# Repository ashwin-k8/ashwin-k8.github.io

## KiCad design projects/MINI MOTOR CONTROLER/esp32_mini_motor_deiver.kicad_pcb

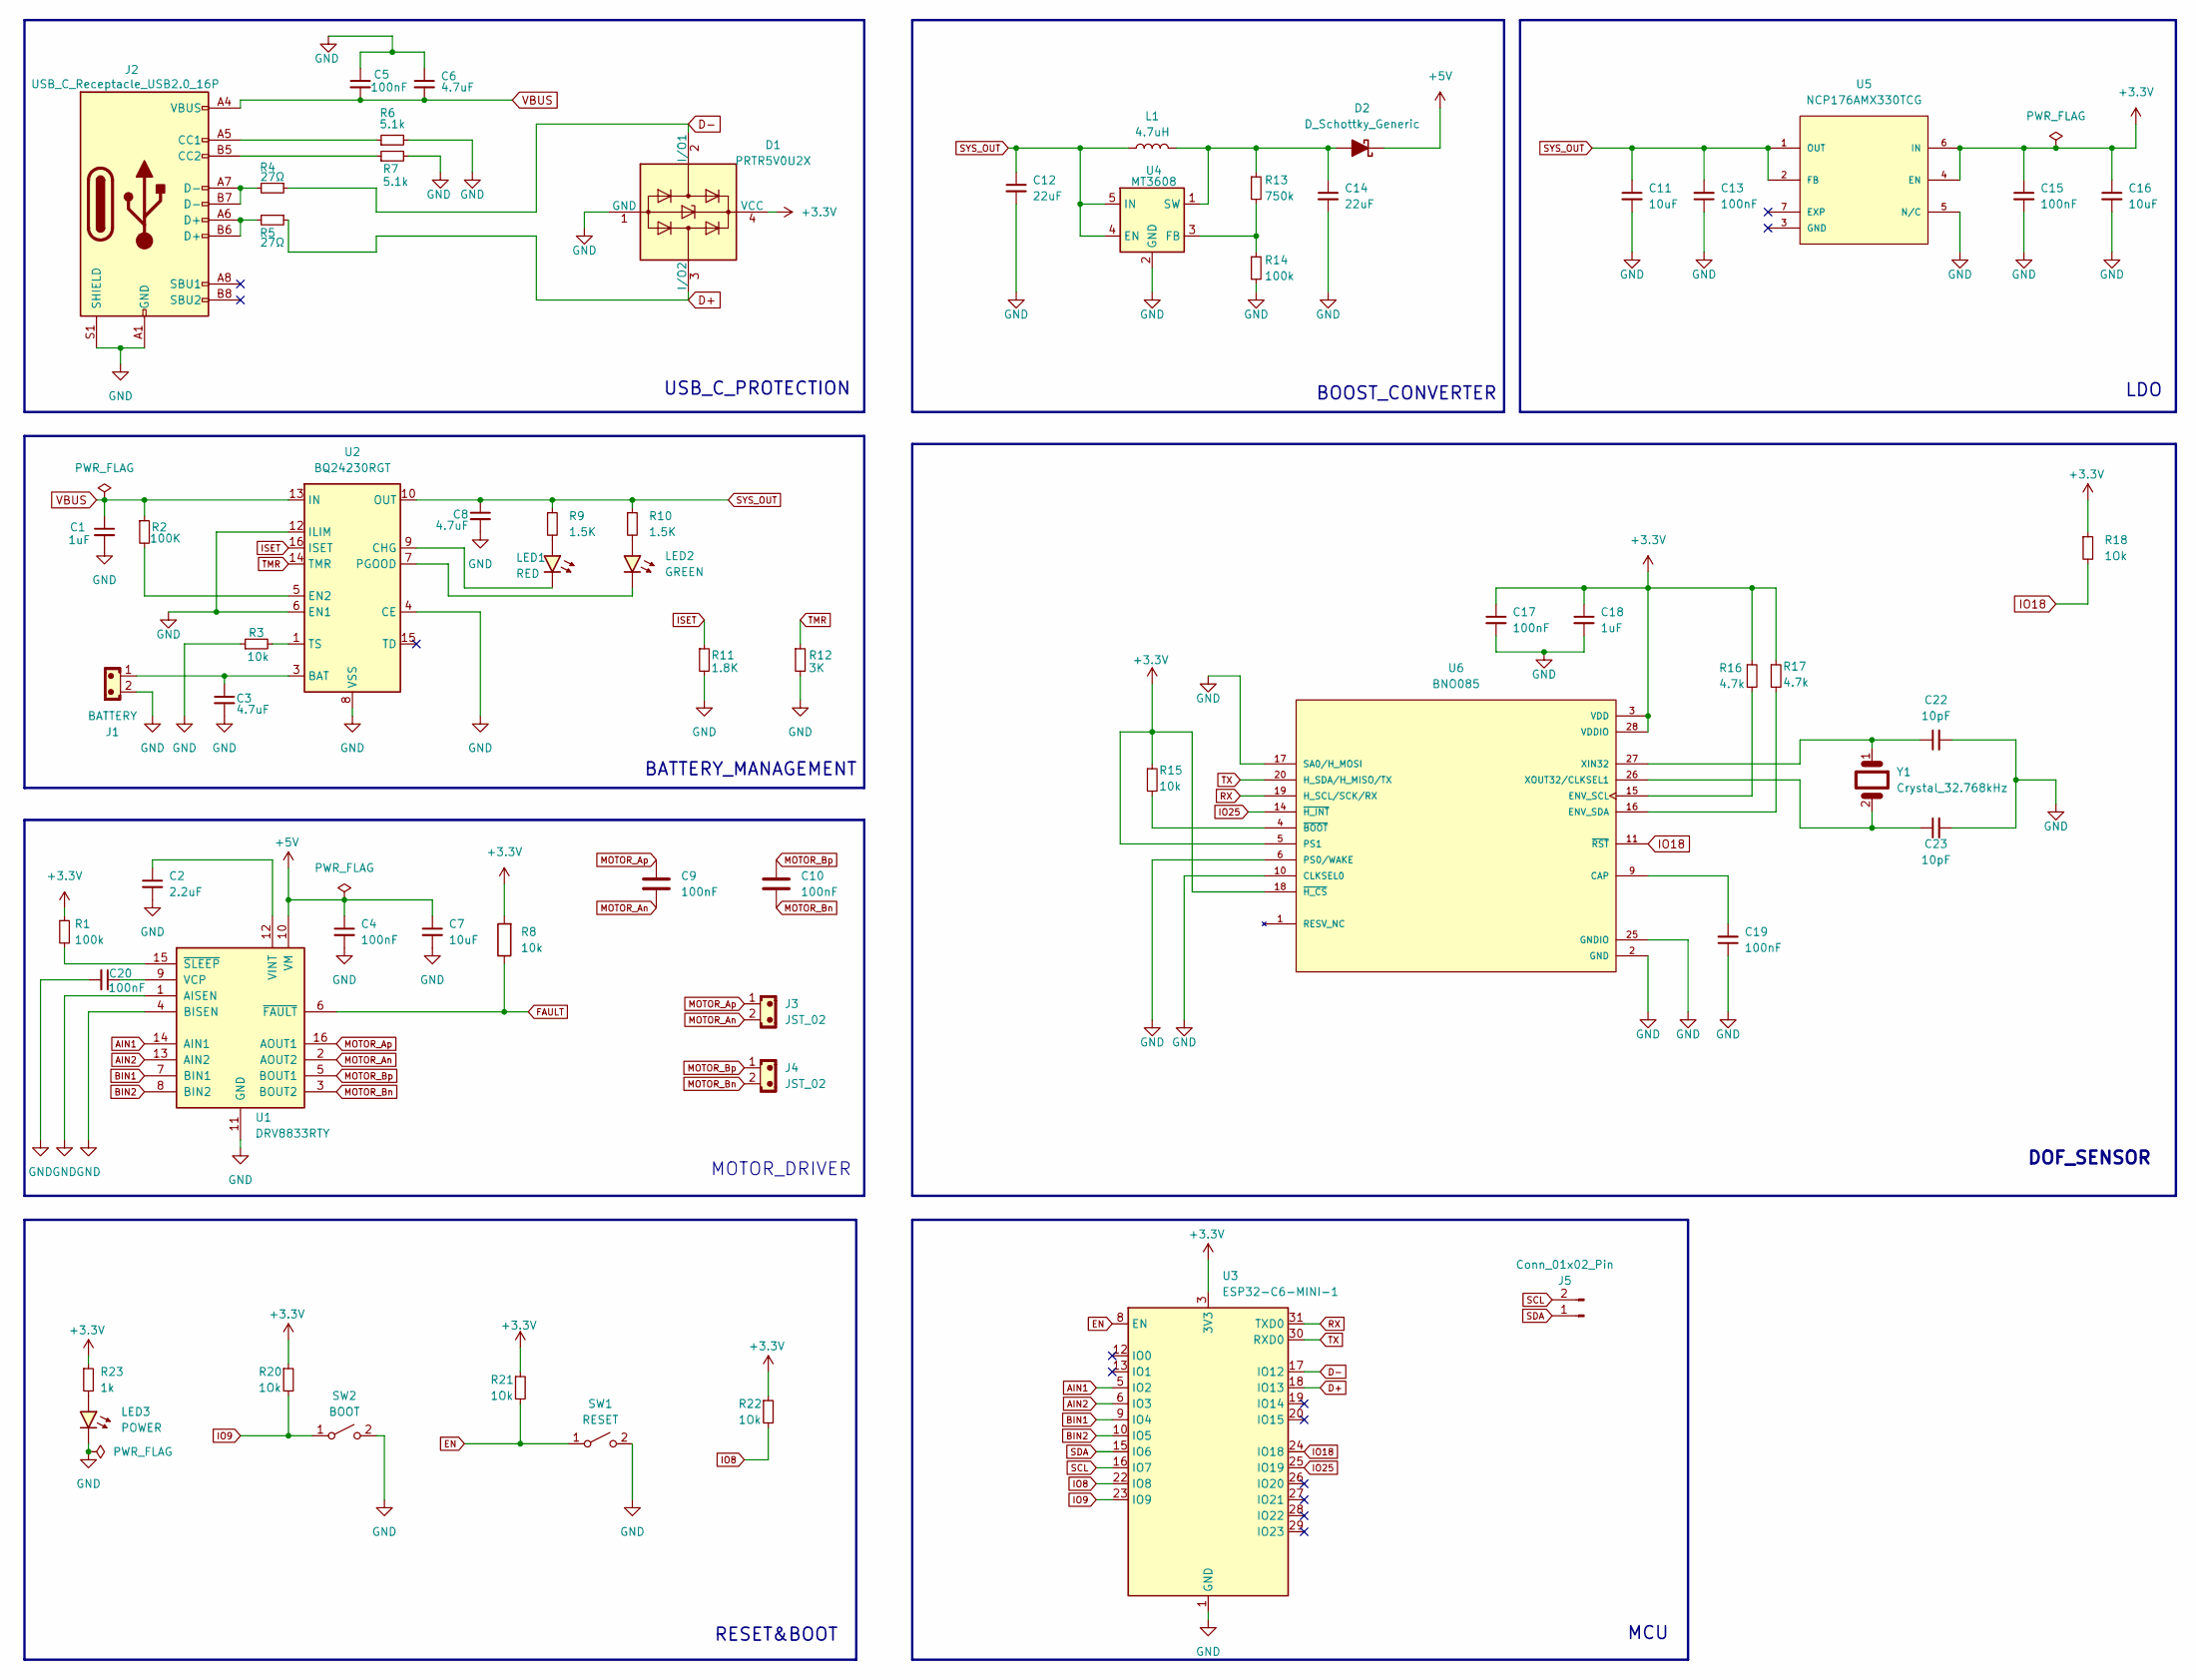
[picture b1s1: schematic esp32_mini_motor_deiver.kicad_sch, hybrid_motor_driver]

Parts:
C1: 1uF; C_0603_1608Metric
C2: 2.2uF; C_0603_1608Metric
C3, C6, C8: 4.7uF; C_0603_1608Metric
C4, C5: 100nF; C_0603_1608Metric
C7: 10uF; C_0603_1608Metric
C9, C10: 100nF; C_0402_1005Metric
C11, C16: 10uF; C_0805_2012Metric
C12, C14: 22uF; C_0805_2012Metric
C13, C15, C17, C19, C20: 100nF; C_0805_2012Metric
C18: 1uF; C_0805_2012Metric
C22, C23: 10pF; C_0805_2012Metric
D1: PRTR5V0U2X; SOT-143
D2: D_Schottky_Generic; D_0603_1608Metric
J1: BATTERY; JST_SH_SM02B-SRSS-TB_1x02-1MP_P1.00mm_Horizontal
J2: USB_C_Receptacle_USB2.0_16P; USB_C_Receptacle_XKB_U262-16XN-4BVC11
J3, J4: JST_02; JST_EH_B2B-EH-A_1x02_P2.50mm_Vertical
J5: Conn_01x02_Pin; PinHeader_1x02_P1.00mm_Vertical
L1: 4.7uH; L_0805_2012Metric
LED1: RED; LED_0603_1608Metric
LED2: GREEN; LED_0603_1608Metric
LED3: POWER; LED_0805_2012Metric
R1, R14: 100k; R_0805_2012Metric
R2: 100K; R_0805_2012Metric
R3, R8, R15: 10k; R_0805_2012Metric
R4, R5: 27Ω; R_0805_2012Metric
R6, R7: 5.1k; R_0805_2012Metric
R9, R10: 1.5K; R_0805_2012Metric
R11: 1.8K; R_0805_2012Metric
R12: 3K; R_0805_2012Metric
R13: 750k; R_0805_2012Metric
R16, R17: 4.7k; R_0805_2012Metric
R18, R20, R21, R22: 1Ok; R_0805_2012Metric
R23: 1k; R_0805_2012Metric
SW1: RESET; SW_SPST_B3U-1000P
SW2: BOOT; SW_SPST_B3U-1000P
U1: DRV8833RTY; Texas_RTY_WQFN-16-1EP_4x4mm_P0.65mm_EP2.1x2.1mm_ThermalVias
U2: BQ24230RGT; VQFN-16-1EP_3x3mm_P0.5mm_EP1.68x1.68mm_ThermalVias
U3: ESP32-C6-MINI-1
U4: MT3608; SOT-23-6
U5: NCP176AMX330TCG; PARTREV 5
U6: BNO085; PARTREV v1.17
Y1: Crystal_32.768kHz; Crystal_SMD_EuroQuartz_EQ161-2Pin_3.2x1.5mm

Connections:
+3.3V: C15.1, C16.1, C17.1, C18.1, D1.4 (VCC), R1.1, R8.2, R15.1, R16.1, R17.1, R18.1, R20.1, R21.1, R22.1, R23.1, U3.3 (3V3), U5.4 (EN), U5.6 (IN), U6.3 (VDD), U6.5 (PS1), U6.18 (~H_CS), U6.28 (VDDIO)
+5V: C4.1, C7.1, D2.1 (K), U1.10 (VM)
AIN1: U1.14 (AIN1), U3.5 (IO2)
AIN2: U1.13 (AIN2), U3.6 (IO3)
BIN1: U1.7 (BIN1), U3.9 (IO4)
BIN2: U1.8 (BIN2), U3.10 (IO5)
D+: D1.3 (I/O2), R5.1, U3.18 (IO13)
D-: D1.2 (I/O1), R4.1, U3.17 (IO12)
EN: R21.2, SW1.1 (A), U3.8 (EN)
FAULT: R8.1, U1.6 (~FAULT)
GND: C1.2, C2.2, C3.2, C4.2, C5.1, C6.1, C7.2, C8.2, C11.2, C12.2, C13.1, C14.2, C15.2, C16.2, C17.2, C18.2, C19.1, C20.2, C22.2, C23.2, D1.1 (GND), J1.2, J2.A1 (GND_A1), J2.A12 (GND_A12), J2.B1 (GND_B1), J2.B12 (GND_B12), J2.S1 (SHIELD), J2.SH (SHIELD_S1), LED3.1 (K), R3.1, R6.2, R7.2, R11.2, R12.2, R14.2, SW1.2 (B), SW2.2 (B), U1.1 (AISEN), U1.4 (BISEN), U1.11 (GND), U1.17 (GND), U2.4 (CE), U2.6 (EN1), U2.8 (VSS), U2.12 (ILIM), U2.17 (VSS), U3.1 (GND), U3.2 (GND), U3.11 (GND), U3.14 (GND), U3.36 (GND), U3.37 (GND), U3.38 (GND), U3.39 (GND), U3.40 (GND), U3.41 (GND), U3.42 (GND), U3.43 (GND), U3.44 (GND), U3.45 (GND), U3.46 (GND), U3.47 (GND), U3.48 (GND), U3.49 (GND), U3.50 (GND), U3.51 (GND), U3.52 (GND), U3.53 (GND), U4.2 (GND), U5.5 (N/C), U6.2 (GND), U6.6 (PS0/WAKE), U6.10 (CLKSEL0), U6.17 (SA0/H_MOSI), U6.25 (GNDIO); also elsewhere on the board
IO8: R22.2, U3.22 (IO8)
IO9: R20.2, SW2.1 (A), U3.23 (IO9); also elsewhere on the board
IO18: R18.2, U3.24 (IO18), U6.11 (~RST)
IO25: U3.25 (IO19), U6.14 (~H_INT)
ISET: R11.1, U2.16 (ISET)
MOTOR_An: C9.2, J3.2, U1.2 (AOUT2)
MOTOR_Ap: C9.1, J3.1, U1.16 (AOUT1)
MOTOR_Bn: C10.2, J4.2, U1.3 (BOUT2)
MOTOR_Bp: C10.1, J4.1, U1.5 (BOUT1)
unnamed: C3.1, J1.1, U2.2 (BAT), U2.3 (BAT)
unnamed: C14.1, D2.2 (A), L1.2, R13.1, U4.1 (SW)
unnamed: J2.A5 (CC1_A5), R6.1
unnamed: J2.B5 (CC2_B5), R7.1
unnamed: J2.A6 (D+_A6), J2.B6 (D+_B6), R5.2
unnamed: J2.A7 (D-_A7), J2.B7 (D-_B7), R4.2
unnamed: LED1.2 (A), R9.2
unnamed: LED1.1 (K), U2.9 (CHG)
unnamed: LED2.2 (A), R10.2
unnamed: LED2.1 (K), U2.7 (PGOOD)
unnamed: LED3.2 (A), R23.2
unnamed: C20.1, U1.9 (VCP)
unnamed: C2.1, U1.12 (VINT)
unnamed: R1.2, U1.15 (~SLEEP)
unnamed: R2.2, U2.5 (EN2)
unnamed: R3.2, U2.1 (TS)
unnamed: R13.2, R14.1, U4.3 (FB)
unnamed: C19.2, U6.9 (CAP)
unnamed: R16.2, U6.15 (ENV_SCL)
unnamed: R17.2, U6.16 (ENV_SDA)
unnamed: C22.1, U6.27 (XIN32), Y1.1
unnamed: C23.1, U6.26 (XOUT32/CLKSEL1), Y1.2
unnamed: R15.2, U6.4 (~BOOT)
RX: U3.31 (TXD0), U6.19 (H_SCL/SCK/RX)
SCL: J5.2, U3.16 (IO7)
SDA: J5.1, U3.15 (IO6)
SYS_OUT: C8.1, C11.1, C12.1, C13.2, L1.1, R9.1, R10.1, U2.10 (OUT), U2.11 (OUT), U4.4 (EN), U4.5 (IN), U5.1 (OUT), U5.2 (FB)
TMR: R12.1, U2.14 (TMR)
TX: U3.30 (RXD0), U6.20 (H_SDA/H_MISO/TX)
VBUS: C1.1, C5.2, C6.2, J2.A4 (VBUS_A4), J2.A9 (VBUS_A9), J2.B4 (VBUS_B4), J2.B9 (VBUS_B9), R2.1, U2.13 (IN)

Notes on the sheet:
DOF_SENSOR
BATTERY_MANAGEMENT
MOTOR_DRIVER
MCU
BOOST_CONVERTER
LDO
RESET&BOOT
USB_C_PROTECTION

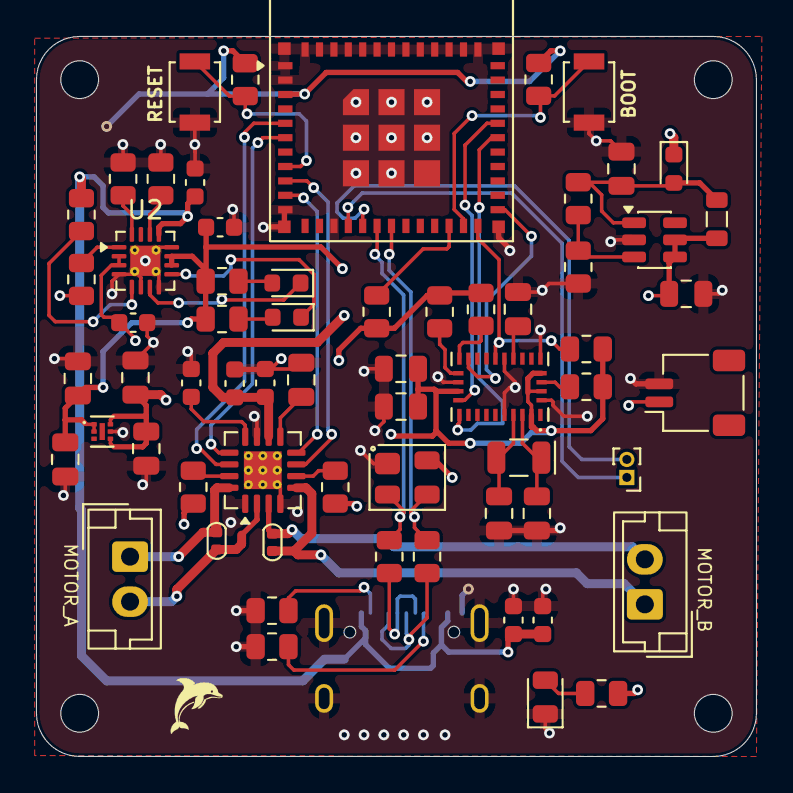
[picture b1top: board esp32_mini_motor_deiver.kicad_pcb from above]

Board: 4 copper layers, 40.0 x 40.0 mm, 64 parts (1 on the bottom side), 50 nets.

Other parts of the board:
BOOT: BOOT; SW_SPST_B3U-1000P

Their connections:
GND: BOOT.2 (B); also elsewhere on the board
IO9: BOOT.1 (A); also elsewhere on the board

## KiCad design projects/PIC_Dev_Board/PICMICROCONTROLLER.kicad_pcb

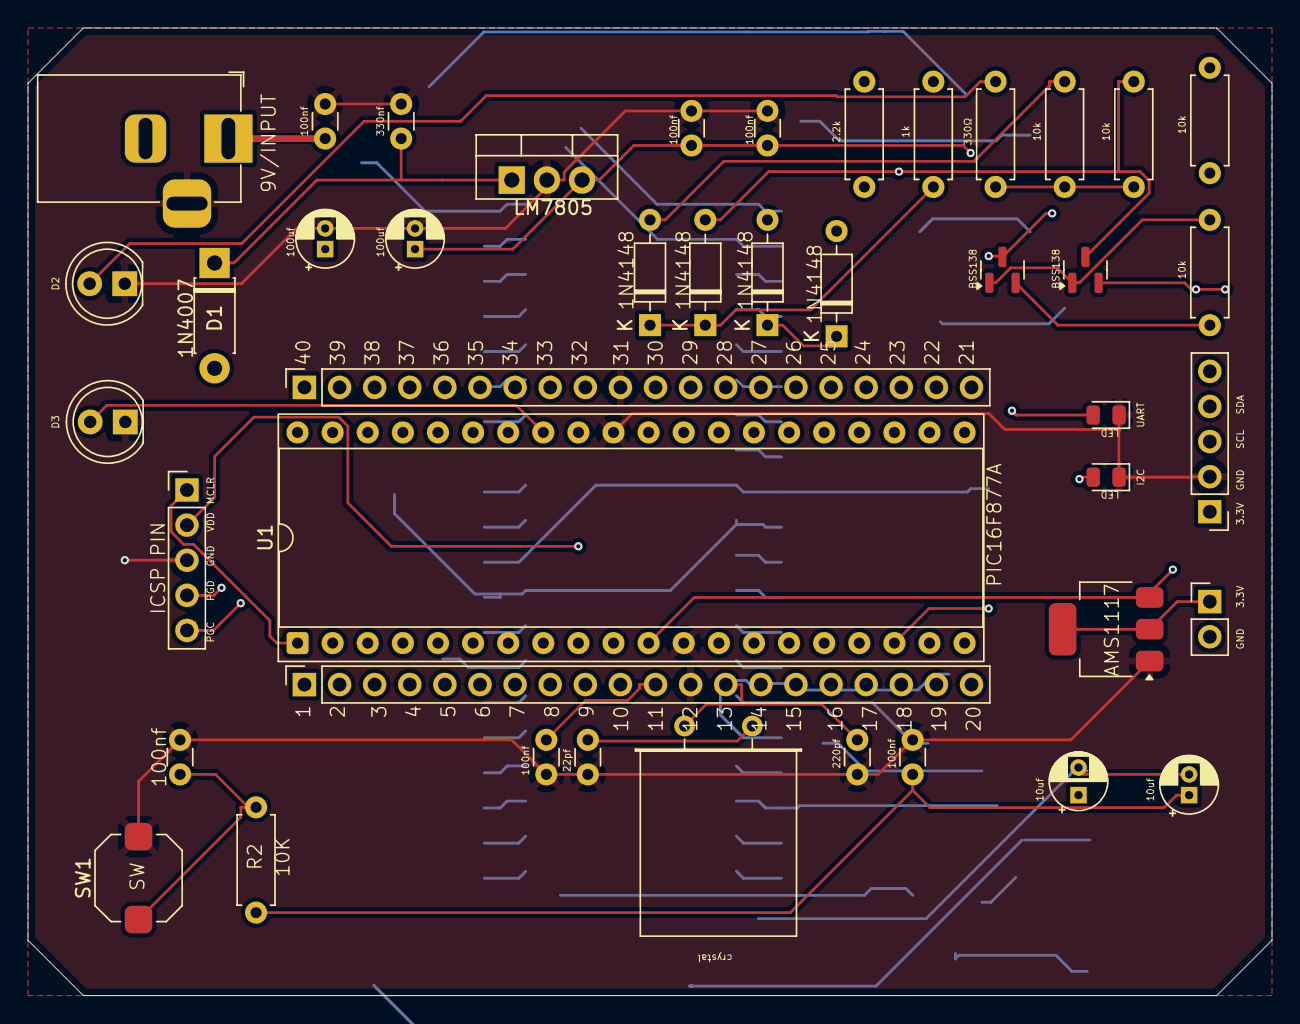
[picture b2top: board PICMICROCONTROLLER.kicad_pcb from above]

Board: 2 copper layers, 90.0 x 70.0 mm, 43 parts (0 on the bottom side), 48 nets.

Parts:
1k: 1k; R_Axial_DIN0207_L6.3mm_D2.5mm_P7.62mm_Horizontal
2.2k: 2.2k; R_Axial_DIN0207_L6.3mm_D2.5mm_P7.62mm_Horizontal
10k, 10k#2, 10k#3, 10k#4: 10k; R_Axial_DIN0207_L6.3mm_D2.5mm_P7.62mm_Horizontal
22pf, 220pf: 22pF; C_Disc_D3.0mm_W1.6mm_P2.50mm
100nf, 100nf#3: 100nF_Ceramic; C_Disc_D3.0mm_W1.6mm_P2.50mm
100nf#2: 100nF; C_Disc_D3.0mm_W1.6mm_P2.50mm
100uf: 10uF/10v; CP_Radial_D4.0mm_P1.50mm
100uf#2: 100uF/25V; CP_Radial_D4.0mm_P1.50mm
330nf: 330nF; C_Disc_D3.0mm_W1.6mm_P2.50mm
330Ω: 330Ω; R_Axial_DIN0207_L6.3mm_D2.5mm_P7.62mm_Horizontal
C4, C6, C9: 100nF; C_Disc_D3.0mm_W1.6mm_P2.50mm
C12: 10uF_16V; CP_Radial_D4.0mm_P1.50mm
C13: 10uF_16V; CP_Radial_D4.0mm_P2.00mm
D1: 1N4007; D_DO-41_SOD81_P7.62mm_Horizontal
D2, D3: LED; LED_D5.0mm
D4, D5, D6, D7: 1N4148; D_DO-35_SOD27_P7.62mm_Horizontal
I2C: LED; LED_0805_2012Metric
J1: PINHD_1x4_Female; PinHeader_1x05_P2.54mm_Vertical
J2: Barrel_Jack_Switch; BarrelJack_Horizontal
J3, J4: Conn_01x20_Pin; PinSocket_1x20_P2.54mm_Vertical
J5: Conn_01x05_Socket; PinHeader_1x05_P2.54mm_Vertical
J8: PINHD_1x2_Female; PinHeader_1x02_P2.54mm_Vertical
LM7805: LM7805; TO-220-3_Vertical
Q1, Q2: BSS138; SOT-23
R2: 10k; R_Axial_DIN0207_L6.3mm_D2.5mm_P7.62mm_Horizontal
SW1: SW_Push; SW_Push_1TS009xxxx-xxxx-xxxx_6x6x5mm
U1: PIC16F877A-IP; DIP-40_W15.24mm_Socket
U3: AMS1117; SOT-223-3_TabPin2
UART: LED; LED_0805_2012Metric
Y1: Crystal; Crystal_HC49-U_Horizontal

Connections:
3.3V: 10k.2, 10k#2.2, C13.1, J1.1, J8.1, Q1.1 (G), Q2.1 (G), U3.2 (VO)
/MCLR: C9.1, J3.1, J5.1, R2.2, SW1.1, U1.1 (~MCLR/Vpp)
/PGC: J4.2, J5.5, U1.39 (PGC/RB6)
/PGD: J4.1, J5.4, U1.40 (PGD/RB7)
/PIN2: J3.2, U1.2 (AN0/RA0)
/PIN3: J3.3, U1.3 (AN1/RA1)
/PIN4: J3.4, U1.4 (CVref/Vref-/AN2/RA2)
/PIN5: J3.5, U1.5 (Vref+/AN3/RA3)
/PIN6: J3.6, U1.6 (C1OUT/T0CKI/RA4)
/PIN7: J3.7, U1.7 (~SS/C2OUT/AN4/RA5)
/PIN9: J3.9, U1.9 (RE1/~WR/AN6)
/PIN10: J3.10, U1.10 (RE2/~CS/AN7)
/PIN13: 220pf.2, J3.13, U1.13 (OSC1/CLKI), Y1.1
/PIN14: 22pf.2, J3.14, U1.14 (OSC2/CLKO), Y1.2
/PIN15: J3.15, U1.15 (T1OSO/T1CKI/RC0)
/PIN16: J3.16, U1.16 (T1OSI/CCP2/RC1)
/PIN17: J3.17, U1.17 (CCP1/RC2)
/PIN18: 10k#4.2, D4.2 (A), J3.18, Q2.3 (D), U1.18 (SCK/SCL/RC3)
/PIN19: J3.19, U1.19 (RD0/PSP0)
/PIN20: J3.20, U1.20 (RD1/PSP1)
/PIN21: J4.20, U1.21 (RD2/PSP2)
/PIN22: J4.19, U1.22 (RD3/PSP3)
/PIN23: 10k#3.2, D5.2 (A), J4.18, Q1.3 (D), U1.23 (SDI/SDA/RC4)
/PIN24: J4.17, U1.24 (SDO/RC5)
/PIN25: D6.2 (A), J4.16, U1.25 (CK/TX/RC6)
/PIN26: D7.2 (A), J4.15, U1.26 (DT/RX/RC7)
/PIN27: J4.14, U1.27 (RD4/PSP4)
/PIN28: J4.13, U1.28 (RD5/PSP5)
/PIN29: J4.12, U1.29 (RD6/PSP6)
/PIN30: J4.11, U1.30 (RD7/PSP7)
/PIN33: D3.2, J4.8, U1.33 (INT/RB0)
/PIN34: J4.7, U1.34 (RB1)
/PIN35: J4.6, U1.35 (RB2)
/PIN36: J4.5, U1.36 (PGM/RB3)
/PIN37: J4.4, U1.37 (RB4)
/PIN38: J4.3, U1.38 (RB5)
GND: 22pf.1, 100nf.1, 100nf#2.2, 100nf#3.2, 100uf.2, 100uf#2.2, 220pf.1, 330nf.2, C4.2, C6.2, C9.2, D2.1 (K), D3.1, I2C.1, J1.2, J2.3, J3.12, J4.10, J5.3, LM7805.2 (GND), SW1.2, U1.12 (VSS), U1.31 (VSS), U3.1 (GND), UART.1
unnamed: C12.2, C13.2, J8.2
unnamed: 100nf#2.1, 100uf#2.1, D1.2 (A), J2.1
unnamed: 330nf.1, D1.1 (K), LM7805.1 (VI)
unnamed: 330Ω.2, D2.2 (A)
unnamed: 1k.1, D4.1 (K), D5.1 (K)
unnamed: 2.2k.1, D6.1 (K), D7.1 (K)
unnamed: 1k.2, I2C.2
unnamed: 2.2k.2, UART.2
unnamed: 10k.1, J1.4, Q1.2 (S)
unnamed: 10k#2.1, J1.3, Q2.2 (S)
VDD: 10k#3.1, 10k#4.1, 100nf.2, 100nf#3.1, 100uf.1, 330Ω.1, C4.1, C6.1, C12.1, J3.11, J4.9, J5.2, LM7805.3 (VO), R2.1, U1.11 (VDD), U1.32 (VDD), U3.3 (VI)

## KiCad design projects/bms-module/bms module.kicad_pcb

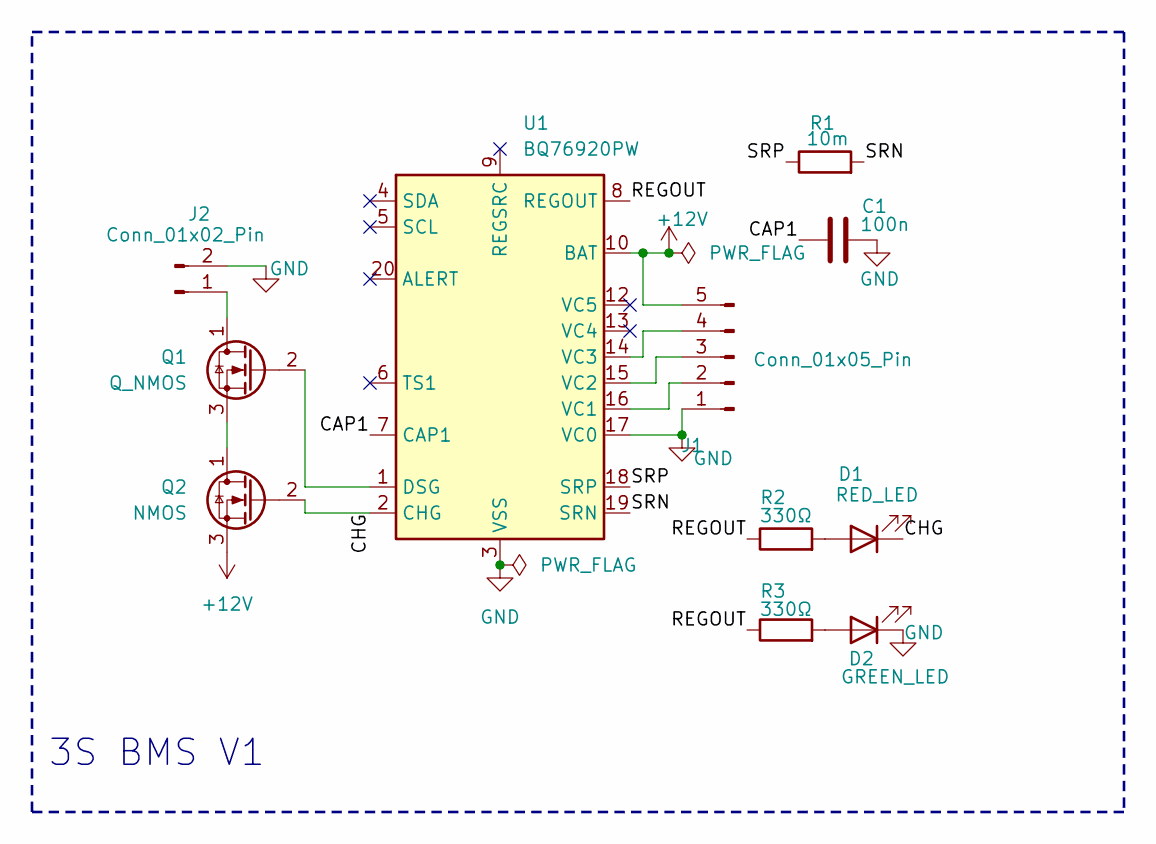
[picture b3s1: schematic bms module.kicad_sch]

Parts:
C1: 100n; C_0402_1005Metric
D1: RED_LED; LED_0402_1005Metric
D2: GREEN_LED; LED_0402_1005Metric
J1: Conn_01x05_Pin; PinHeader_1x05_P2.54mm_Vertical
J2: Conn_01x02_Pin; PinHeader_1x02_P2.54mm_Vertical
Q1: Q_NMOS; SOT-23
Q2: NMOS; SOT-23
R1: 10m; R_2512_6332Metric
R2, R3: 330Ω; R_0402_1005Metric
U1: BQ76920PW; TSSOP-20_4.4x6.5mm_P0.65mm

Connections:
+12V: J1.5, Q2.3 (S), U1.10 (BAT)
/CAP1: C1.1, U1.7 (CAP1)
/CHG: D1.1 (K), Q2.2 (G), U1.2 (CHG)
/REGOUT: R2.1, R3.1, U1.8 (REGOUT)
/SRN: R1.2, U1.19 (SRN)
/SRP: R1.1, U1.18 (SRP)
GND: C1.2, D2.1 (K), J1.1, J2.2, U1.3 (VSS), U1.17 (VC0)
unnamed: D1.2 (A), R2.2
unnamed: D2.2 (A), R3.2
unnamed: J1.2, U1.16 (VC1)
unnamed: J1.3, U1.15 (VC2)
unnamed: J1.4, U1.14 (VC3)
unnamed: J2.1, Q1.1 (D)
unnamed: Q1.2 (G), U1.1 (DSG)
unnamed: Q1.3 (S), Q2.1 (D)

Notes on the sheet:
3S BMS V1

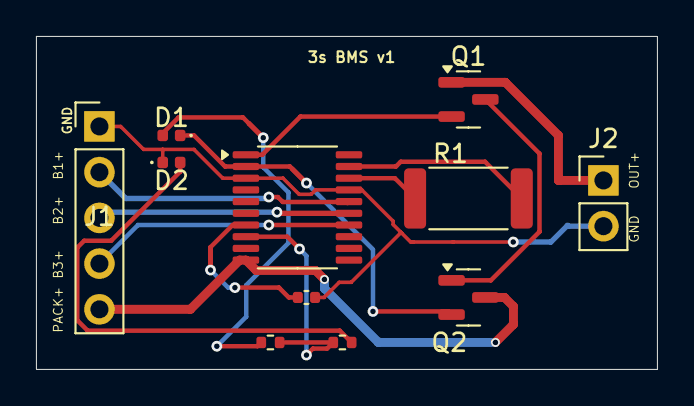
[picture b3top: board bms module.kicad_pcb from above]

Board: 2 copper layers, 34.5 x 18.5 mm, 11 parts (0 on the bottom side), 15 nets.

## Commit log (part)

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2026-05-17 Add initial portfolio HTML structure
2026-05-18 Add GitHub Actions workflow for GitHub Pages deployment
    This workflow automates the deployment of static content to GitHub Pages on pushes to the main branch or manually via the Actions tab.
2026-05-19 Implement toggle functionality for features display
    Added a toggle feature for displaying project features.
2026-05-19 Enhance features list with bullet points
    Updated feature list to include bullet points for clarity.
